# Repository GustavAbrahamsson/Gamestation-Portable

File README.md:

# Gamestation-Portable

A portable gaming console with a 128x64 OLED monochrome screen, two D-pads and an ESP32-S2

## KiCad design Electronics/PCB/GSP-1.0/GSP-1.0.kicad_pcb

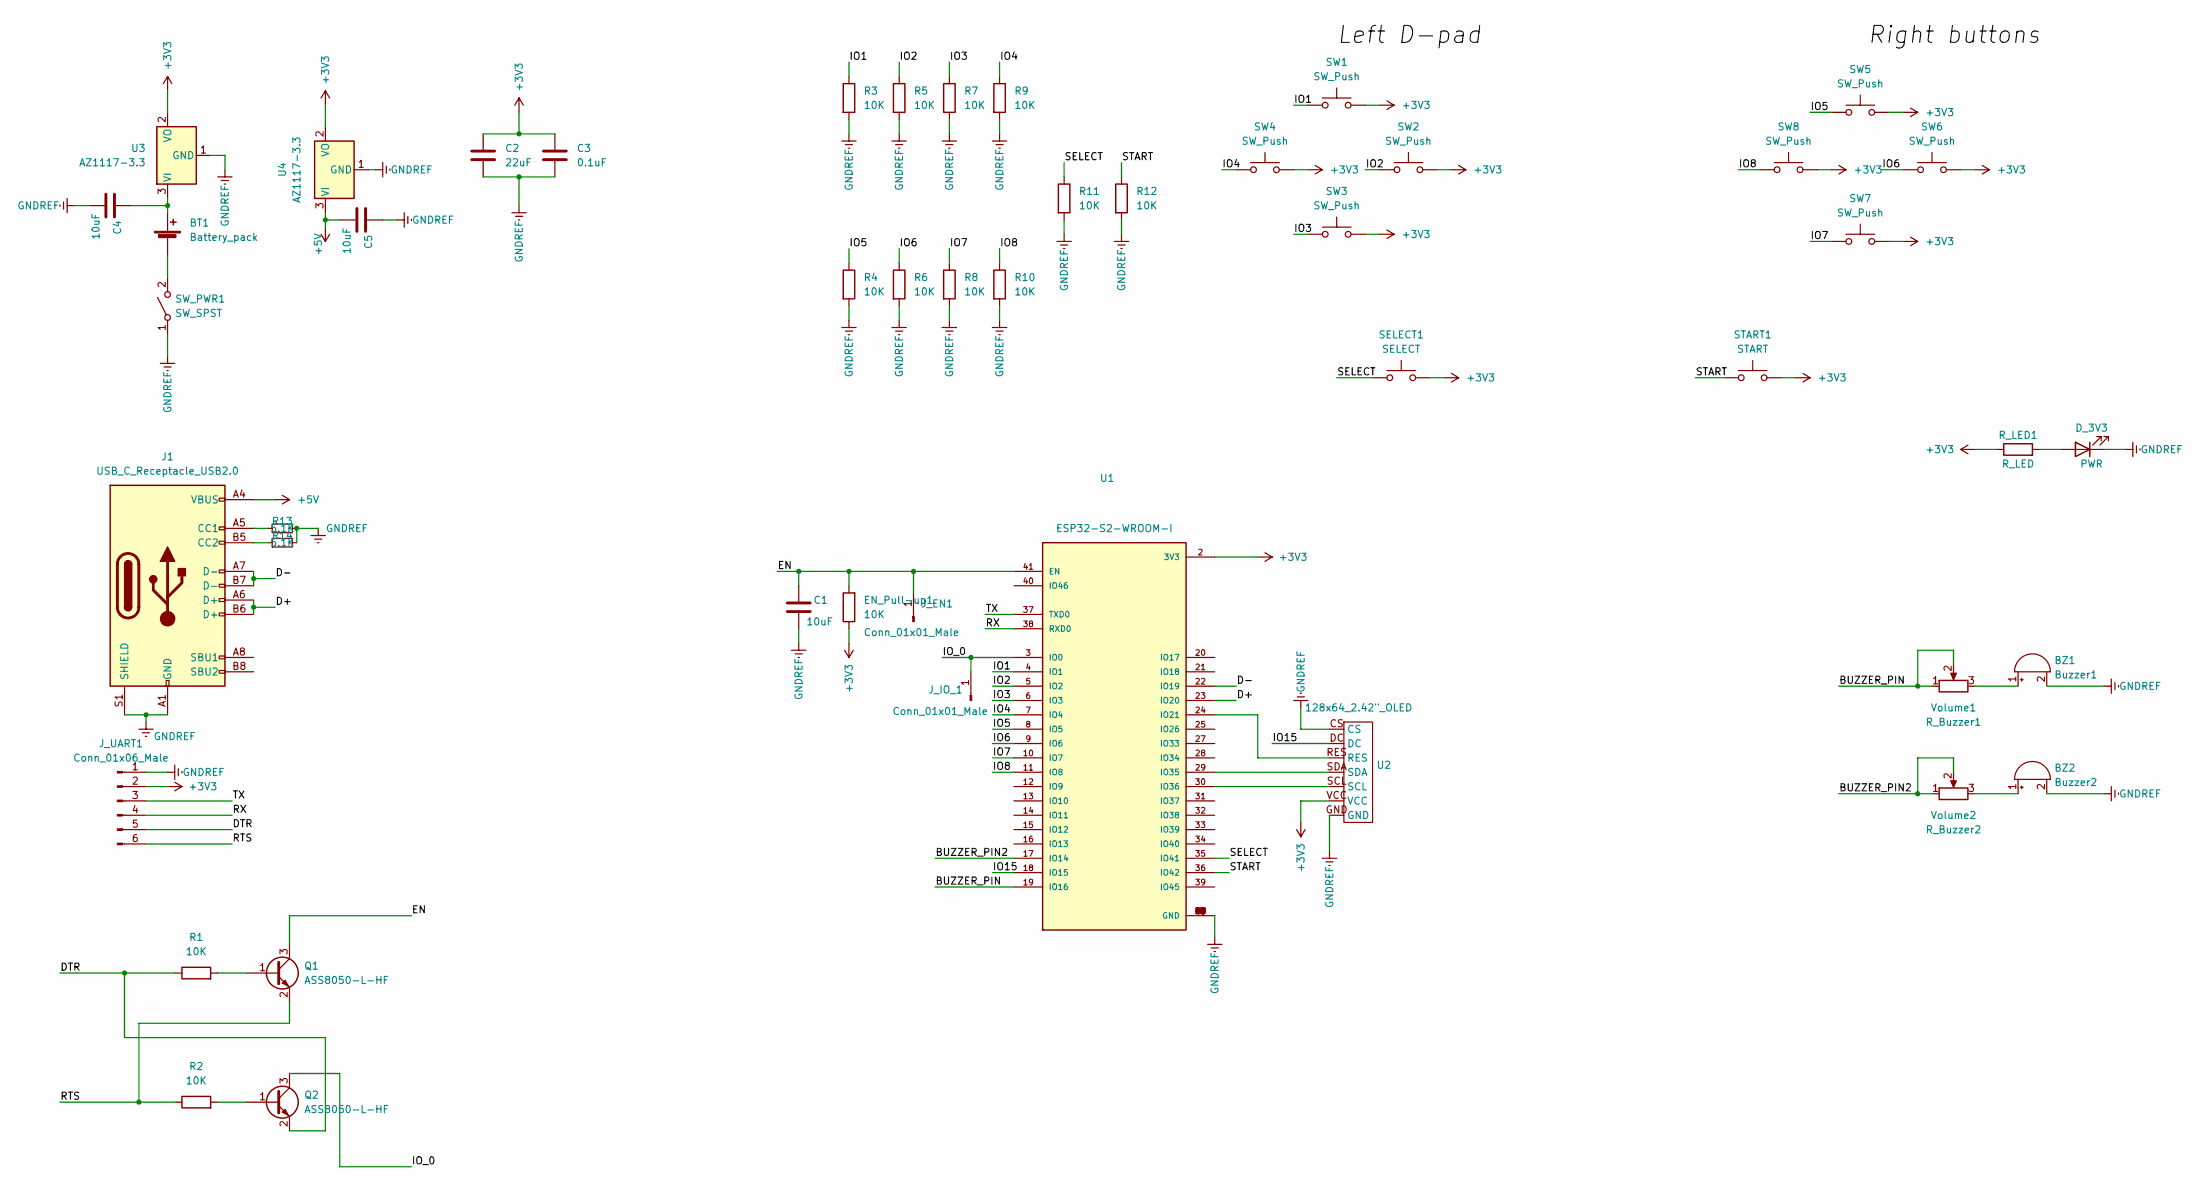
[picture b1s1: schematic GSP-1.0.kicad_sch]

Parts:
BT1: Battery_pack; 3xAA holder (534-2464)
BZ1: Buzzer1; Buzzer_12x9.5RM7.6
BZ2: Buzzer2; Buzzer_12x9.5RM7.6
C1, C4, C5: 10uF; C_0805_2012Metric_Pad1.18x1.45mm_HandSolder
C2: 22uF; C_0805_2012Metric_Pad1.18x1.45mm_HandSolder
C3: 0.1uF; C_0805_2012Metric_Pad1.18x1.45mm_HandSolder
D_3V3: PWR; LED_0805_2012Metric_Pad1.15x1.40mm_HandSolder
EN_Pull-up1: 10K; R_0805_2012Metric_Pad1.20x1.40mm_HandSolder
J1: USB_C_Receptacle_USB2.0; USB_C_Receptacle_HRO_TYPE-C-31-M-12
J_EN1: Conn_01x01_Male; PinHeader_1x01_P1.27mm_Vertical
J_IO_1: Conn_01x01_Male; PinHeader_1x01_P1.27mm_Vertical
J_UART1: Conn_01x06_Male; PinHeader_1x06_P1.27mm_Vertical
Q1, Q2: ASS8050-L-HF; SOT-23
R1, R2, R3, R4, R5, R6, R7, R8, R9, R10, R11, R12: 10K; R_0805_2012Metric_Pad1.20x1.40mm_HandSolder
R13, R14: 5.1K; R_0805_2012Metric_Pad1.20x1.40mm_HandSolder
R_LED1: R_LED; R_0805_2012Metric_Pad1.20x1.40mm_HandSolder
SELECT1: SELECT; SW_Push_1P1T_NO_CK_KSC6xxJ
START1: START; SW_Push_1P1T_NO_CK_KSC6xxJ
SW1, SW2, SW3, SW4, SW5, SW6, SW7, SW8: SW_Push; SW_Push_1P1T_NO_CK_KSC6xxJ
SW_PWR1: SW_SPST; Slide-SW-GF-1123-1110
U1: ESP32-S2-WROOM-I; XCVR_ESP32-S2-WROOM-I; PARTREV v1.3
U2: 128x64_2.42"_OLED; 128x64 2.42 inch OLED display
U3, U4: AZ1117-3.3; SOT-223-3_TabPin2
Volume1: R_Buzzer1; Potentiometer_Alps_RK09K_Single_Horizontal
Volume2: R_Buzzer2; Potentiometer_Alps_RK09K_Single_Horizontal

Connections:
+3V3: C2.1, C3.1, EN_Pull-up1.1, J_UART1.2, R_LED1.1, SELECT1.2, START1.2, SW1.2, SW2.2, SW3.2, SW4.2, SW5.2, SW6.2, SW7.2, SW8.2, U1.2 (3V3), U2.VCC, U3.2 (VO), U4.2 (VO)
+5V: C5.1, J1.A4 (VBUS), J1.A9 (VBUS), J1.B4 (VBUS), J1.B9 (VBUS), U4.3 (VI)
/BUZZER_PIN: U1.19 (IO16), Volume1.1, Volume1.2
/BUZZER_PIN2: U1.17 (IO14), Volume2.1, Volume2.2
/D+: J1.A6 (D+), J1.B6 (D+), U1.23 (IO20)
/D-: J1.A7 (D-), J1.B7 (D-), U1.22 (IO19)
/DTR: J_UART1.5, Q2.2 (E), R1.1
/EN: C1.2, EN_Pull-up1.2, J_EN1.1, Q1.3 (C), U1.41 (EN)
/IO1: R3.1, SW1.1, U1.4 (IO1)
/IO2: R5.1, SW2.1, U1.5 (IO2)
/IO3: R7.1, SW3.1, U1.6 (IO3)
/IO4: R9.1, SW4.1, U1.7 (IO4)
/IO5: R4.1, SW5.1, U1.8 (IO5)
/IO6: R6.1, SW6.1, U1.9 (IO6)
/IO7: R8.1, SW7.1, U1.10 (IO7)
/IO8: R10.1, SW8.1, U1.11 (IO8)
/IO15: U1.18 (IO15), U2.DC
/IO_0: J_IO_1.1, Q2.3 (C), U1.3 (IO0)
/RTS: J_UART1.6, Q1.2 (E), R2.1
/RX: J_UART1.4, U1.38 (RXD0)
/SELECT: R11.1, SELECT1.1, U1.35 (IO41)
/START: R12.1, START1.1, U1.36 (IO42)
/TX: J_UART1.3, U1.37 (TXD0)
GNDREF: BZ1.2 (+), BZ2.2 (+), C1.1, C2.2, C3.2, C4.1, C5.2, D_3V3.1 (K), J1.A1 (GND), J1.A12 (GND), J1.B1 (GND), J1.B12 (GND), J1.S1 (SHIELD), J_UART1.1, R3.2, R4.2, R5.2, R6.2, R7.2, R8.2, R9.2, R10.2, R11.2, R12.2, R13.2, R14.2, SW_PWR1.1 (A), U1.1 (GND), U1.26 (GND), U1.42 (GND), U1.43 (GND), U1.44 (GND), U1.45 (GND), U1.46 (GND), U1.47 (GND), U1.48 (GND), U1.49 (GND), U1.50 (GND), U1.51 (GND), U2.CS, U2.GND, U3.1 (GND), U4.1 (GND)
unnamed: BT1.1 (+), C4.2, U3.3 (VI)
unnamed: BT1.2 (-), SW_PWR1.2 (B)
unnamed: BZ1.1 (-), Volume1.3
unnamed: BZ2.1 (-), Volume2.3
unnamed: D_3V3.2 (A), R_LED1.2
unnamed: J1.A5 (CC1), R13.1
unnamed: J1.B5 (CC2), R14.1
unnamed: Q1.1 (B), R1.2
unnamed: Q2.1 (B), R2.2
unnamed: U1.24 (IO21), U2.RES
unnamed: U1.29 (IO35), U2.SDA
unnamed: U1.30 (IO36), U2.SCL

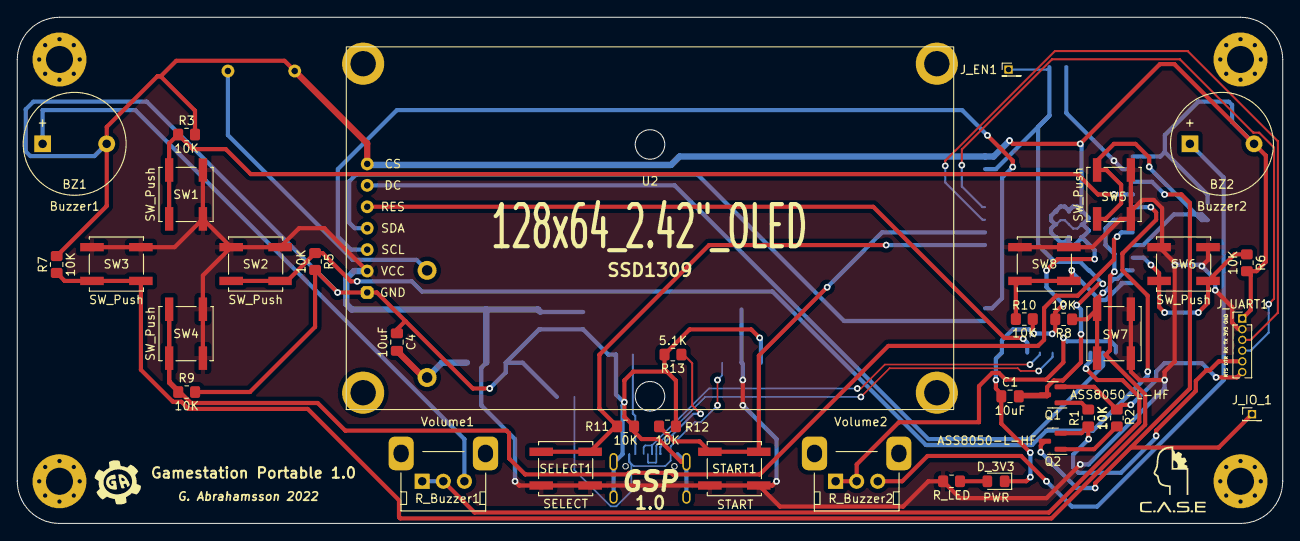
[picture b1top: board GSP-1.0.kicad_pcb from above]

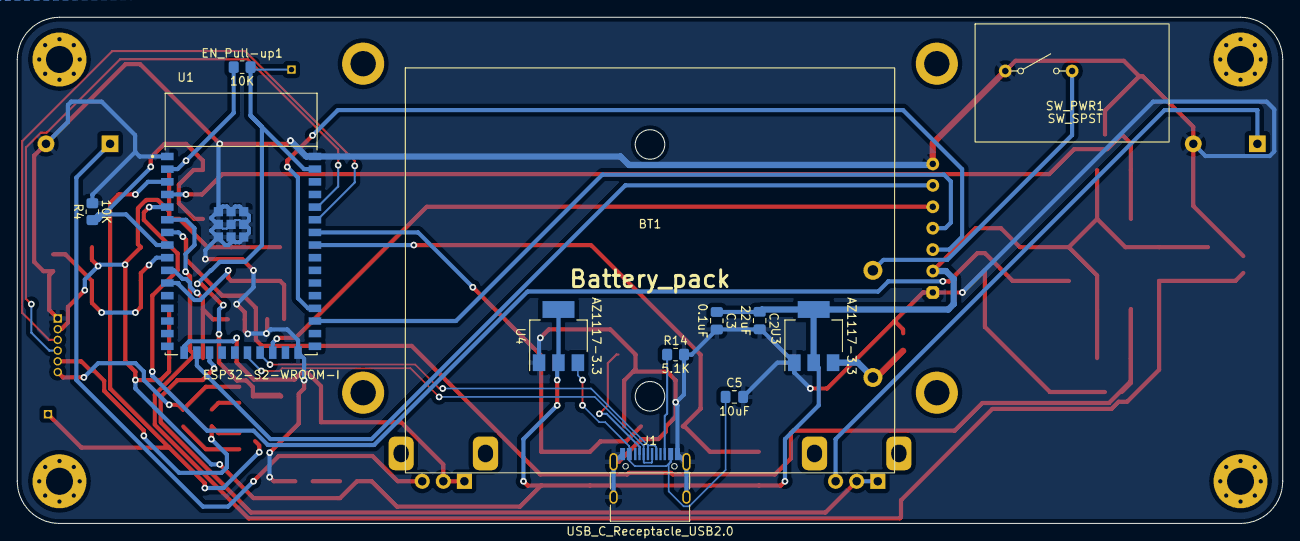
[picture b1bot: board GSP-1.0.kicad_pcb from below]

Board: 2 copper layers, 150.0 x 60.0 mm, 48 parts (12 on the bottom side), 36 nets.

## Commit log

2022-08-08 Implement attempt at Game of Life
2022-08-12 Implement functional Game of Life
2022-08-14 Implement classes, graphics, object handling, Glider-spawner
2022-08-15 Implement rotation of objects, spawn Glider in all 4 directions, render functionality, etc
2022-10-27 Begin PCB
2022-10-30 Fix ESP32 version
2022-10-31 PCB almost finished, but lots of errors
2022-11-02 Fix PCB
2022-11-04 Update PCB
2022-11-06 Final 1.0 version with PCB ordered
2022-11-23 Add code after first assembly of PCB
2022-11-25 Finally able to upload via USB
2022-11-27 Button testing
2022-11-28 Finish buttonHandler and buttonFilter, begin Snake
2022-12-04 Snake progress
    Borders are problematic, the deque manages to move further away
2022-12-04 Working snake with some features missing
2022-12-06 Implement self-bite, game over and bugs
2022-12-09 Add pictures
